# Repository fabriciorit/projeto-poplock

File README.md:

# Trava eletrônica controlada por padrão sonoro
Responsáveis: Caio Vinícius Batista Pereira e Fabrício Ribeiro Toloczko

## Introdução e Justificativa
A automatização residencial tem se tornado cada vez mais comum e mais barata. E uma das facilidades trazidas por este tipo de aplicação tecnológica é a dependência cada vez menor de falhas humanas. É comum as pessoas perderem ou esquecerem as chaves para entrar em casa, e muitas vezes as pessoas tem dificuldades para lembrar senhas. Músicas são trechos sonoros facilmente memorizáveis, além disso extremamente seguros, pois o número de músicas existentes é muito grande e disperso. 

## Especificação do Produto
* Reconhecimento de pelo menos 5 segundos de padrão sonoro;
* Resposta em frequência garantida para frequências médias(200Hz a 1500Hz);
* Tensão de alimentação 110/220V;
* Bateria de emergência;
* Gravação por microfone(eletreto);
* Acionamento de uma trava elétrica 12V de até 1A;
* Comunicação via módulo Wi-Fi usando TCP/IP;
* Interface com usuário via LED;
* Processamento de áudio em servidor alocado em um computador comum.

## Proposta técnica
A pessoa que deseja liberar a trava eletrônica emite um padrão sonoro. Este som é convertido por um sensor(microfone) que alimenta a entrada do microcontrolador. Este, converte o sinal analógico em sinal digital e envia-o pelo módulo de comunicação(Wi-Fi) para um computador, responsável por processar os dados de áudio recebidos.
O computador processará este áudio comparando-o  a um padrão de som de referência previamente configurado, que corresponde à senha de liberação da trava eletrônica. O computador retornará para o microcontrolador um comando de liberação, caso os sinais de áudio sejam considerados iguais, ou de falha de senha, caso os sinais sejam diferentes.
O microcontrolador, por sua vez, aguarda o recebimento de comandos do computador após enviar o som do microfone digitalizado. Ele executará cada comando dependendo de sua função. Duas funções básicas serão destravamento de porta e indicação de falha de senha — via interface com usuário por LED.
Haverá uma fonte de alimentação para os blocos do sistema projetado.

## Proposta de apresentação
Demonstrar o funcionamento do sistema. Este sistema será composto do dispositivo acondicionado em uma caixa plástica e a fechadura representada por uma trava elétrica automotiva — equivalente às de portas residenciais quanto ao princípio de funcionamento. O dispositivo estará ligado a um computador via interface Wi-Fi pela rede convencional.

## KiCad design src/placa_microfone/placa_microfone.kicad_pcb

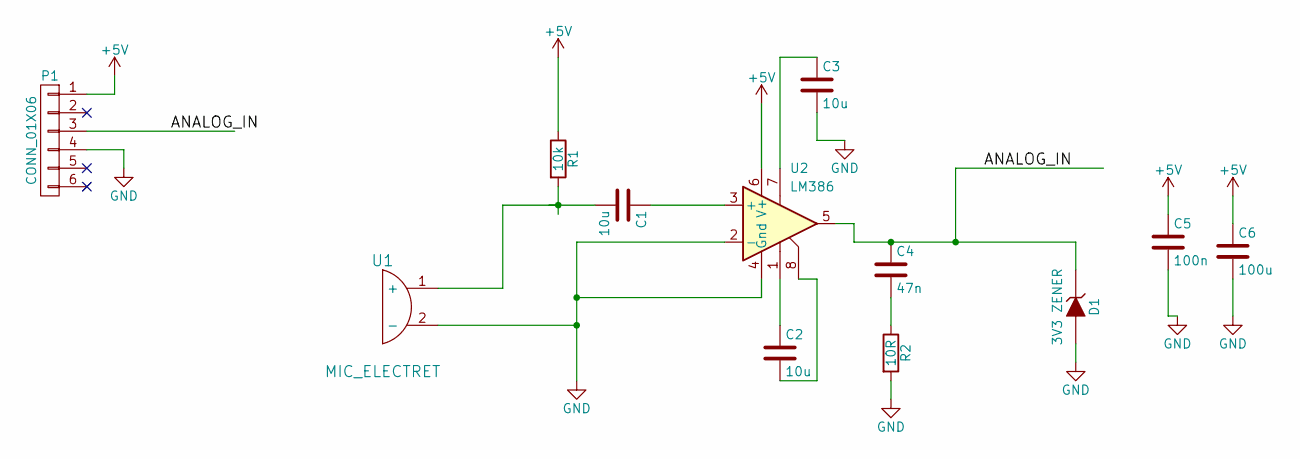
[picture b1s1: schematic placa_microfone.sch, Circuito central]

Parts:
C1, C2, C3: 10u; C_Radial_D5_L6_P2.5
C4: 47n; C_Disc_D3_P2.5
C5: 100n; C_Disc_D3_P2.5
C6: 100u; C_Radial_D5_L6_P2.5
D1: 3V3 ZENER; Diode_DO-35_SOD27_Horizontal_RM10
P1: CONN_01X06; Wafer_Vertical17.5x5.8x7RM2.5-6
R1: 10k; Resistor_Horizontal_RM7mm
R2: 10R; Resistor_Horizontal_RM7mm
U1: MIC_ELECTRET; MagneticBuzzer_Kingstate_KCG0601
U2: LM386; DIP-8_W7.62mm_LongPads

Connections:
+5V: C5.1, C6.1, P1.1, R1.1, U2.6 (V+)
/ANALOG_IN: C4.1, D1.1 (K), P1.3, U2.5
GND: C3.2, C5.2, C6.2, D1.2 (A), P1.4, R2.2, U1.2 (-), U2.2 (-), U2.4 (Gnd)
unnamed: C1.1, U2.3 (+)
unnamed: C1.2, R1.2, U1.1 (+)
unnamed: C2.1, U2.1
unnamed: C2.2, U2.8
unnamed: C3.1, U2.7
unnamed: C4.2, R2.1

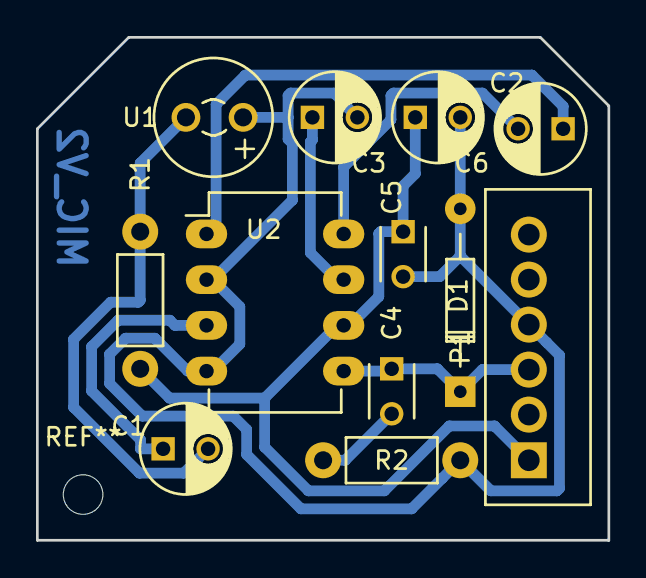
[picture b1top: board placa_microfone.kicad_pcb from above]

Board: 2 copper layers, 31.8 x 27.9 mm, 12 parts (0 on the bottom side), 9 nets.

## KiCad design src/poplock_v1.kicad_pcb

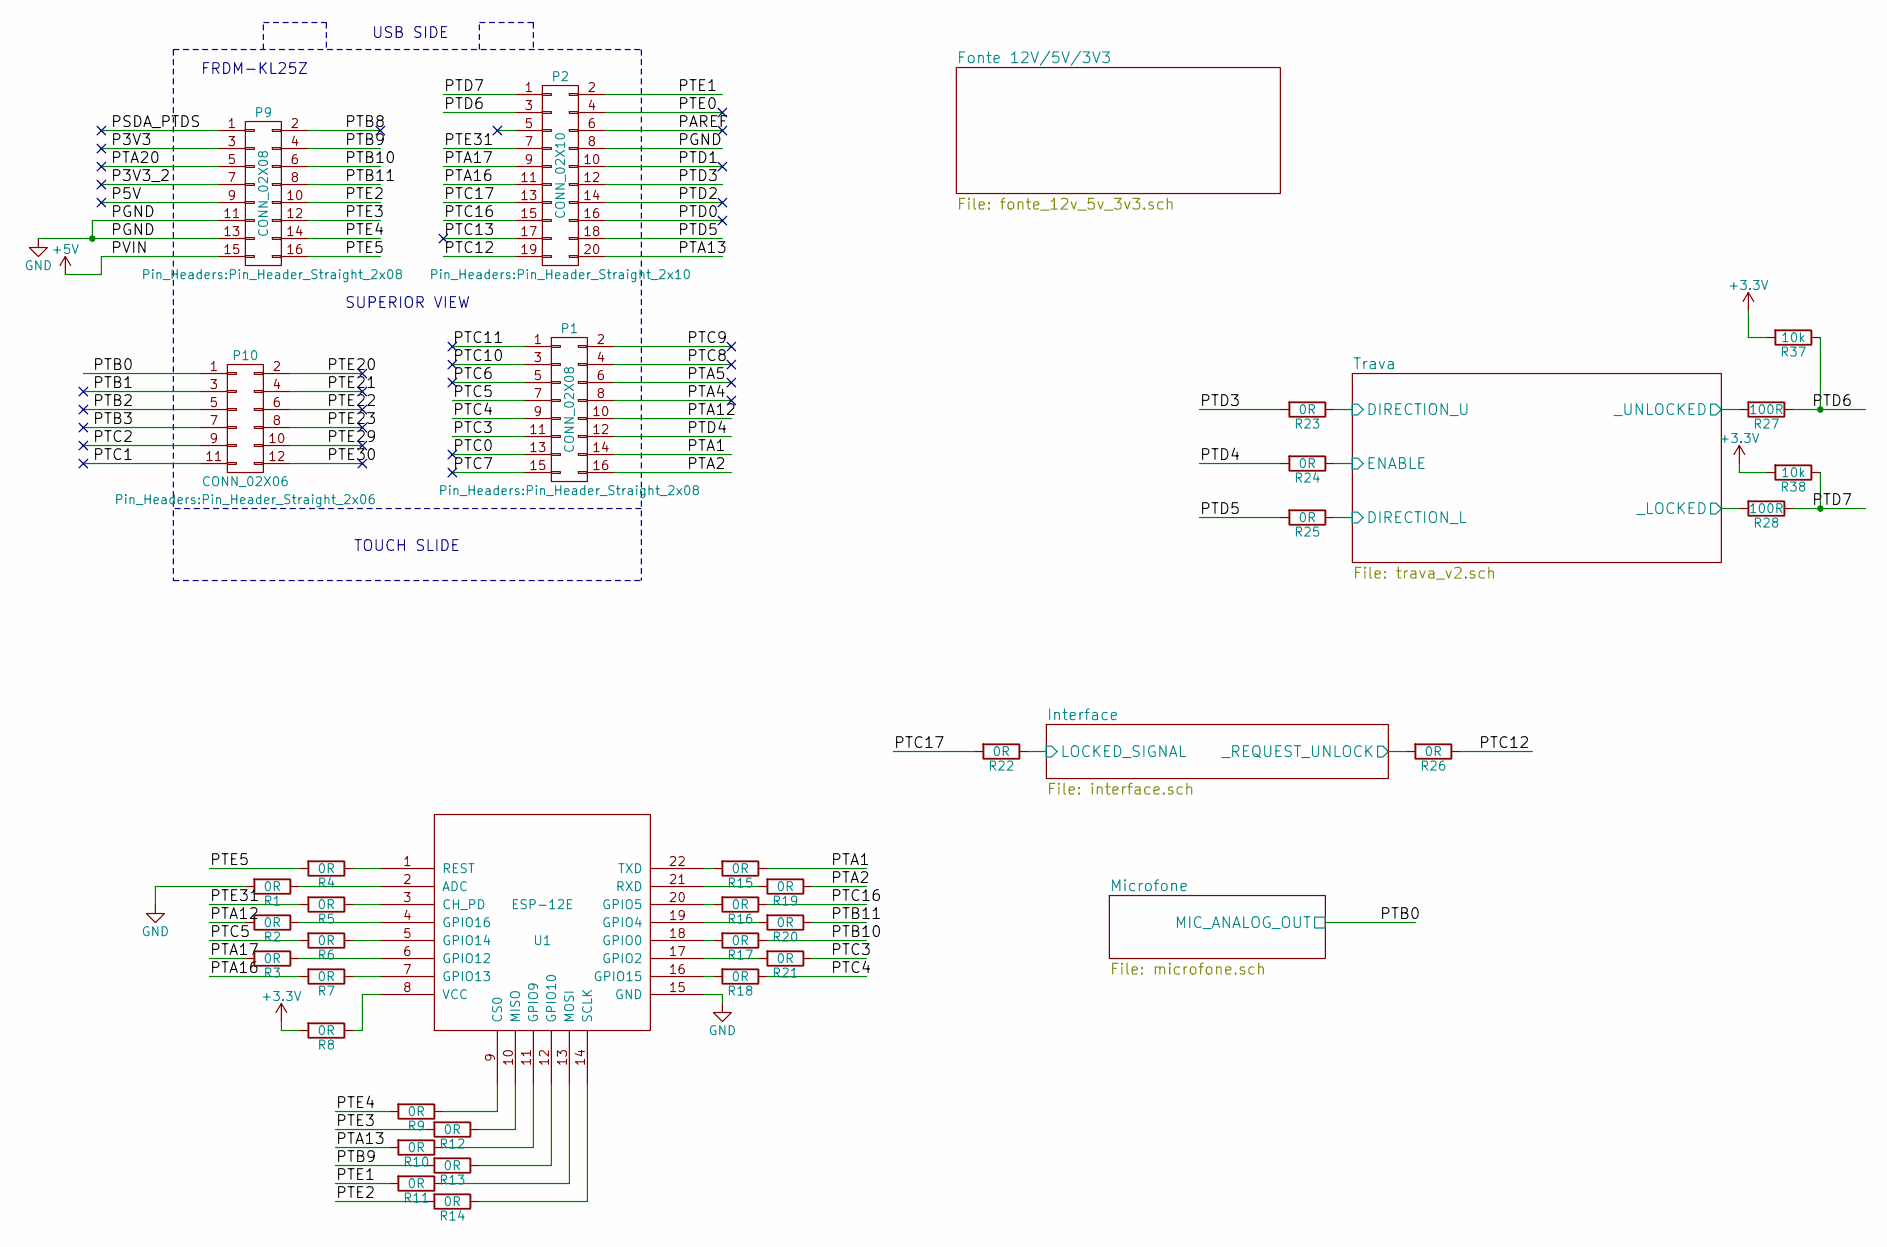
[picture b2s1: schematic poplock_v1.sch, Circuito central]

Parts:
P1, P9: CONN_02X08; Pin_Header_Straight_2x08
P2: CONN_02X10; Pin_Header_Straight_2x10
P10: CONN_02X06; Pin_Header_Straight_2x06
R1, R2, R3, R4, R5, R6, R7, R8, R9, R10, R11, R12, R13, R14, R15, R16, R17, R18, R19, R20, R21, R22, R23, R24, R25, R26: 0R; R_0603_HandSoldering
R27, R28: 100R; R_0603_HandSoldering
R37, R38: 10k; R_0603_HandSoldering
U1: ESP-12E

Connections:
+3V3: R8.2, R37.2, R38.2; also elsewhere on the board
+5V: P9.15; also elsewhere on the board
/Interface/LOCKED_SIGNAL: R22.1; also elsewhere on the board
/Interface/_REQUEST_UNLOCK: R26.2; also elsewhere on the board
/P3V3: P9.3
/P3V3_2: P9.7
/P5V: P9.9
/PAREF: P2.6
/PSDA_PTDS: P9.1
/PTA1: P1.14, R15.1
/PTA2: P1.16, R19.1
/PTA4: P1.8
/PTA5: P1.6
/PTA12: P1.10, R2.2
/PTA13: P2.20, R10.2
/PTA16: P2.11, R7.2
/PTA17: P2.9, R3.2
/PTA20: P9.5
/PTB0: P10.1; also elsewhere on the board
/PTB1: P10.3
/PTB2: P10.5
/PTB3: P10.7
/PTB8: P9.2
/PTB9: P9.4, R13.2
/PTB10: P9.6, R17.1
/PTB11: P9.8, R20.1
/PTC0: P1.13
/PTC1: P10.11
/PTC2: P10.9
/PTC3: P1.11, R21.1
/PTC4: P1.9, R18.1
/PTC5: P1.7, R6.2
/PTC6: P1.5
/PTC7: P1.15
/PTC8: P1.4
/PTC9: P1.2
/PTC10: P1.3
/PTC11: P1.1
/PTC12: P2.19, R26.1
/PTC13: P2.17
/PTC16: P2.15, R16.1
/PTC17: P2.13, R22.2
/PTD0: P2.16
/PTD1: P2.10
/PTD2: P2.14
/PTD3: P2.12, R23.2
/PTD4: P1.12, R24.2
/PTD5: P2.18, R25.2
/PTD6: P2.3, R27.1, R37.1
/PTD7: P2.1, R28.1, R38.1
/PTE0: P2.4
/PTE1: P2.2, R11.2
/PTE2: P9.10, R14.2
/PTE3: P9.12, R12.2
/PTE4: P9.14, R9.2
/PTE5: P9.16, R4.2
/PTE20: P10.2
/PTE21: P10.4
/PTE22: P10.6
/PTE23: P10.8
/PTE29: P10.10
/PTE30: P10.12
/PTE31: P2.7, R5.2
/Trava/DIRECTION_L: R25.1; also elsewhere on the board
/Trava/DIRECTION_U: R23.1; also elsewhere on the board
/Trava/ENABLE: R24.1; also elsewhere on the board
/Trava/_LOCKED: R28.2; also elsewhere on the board
/Trava/_UNLOCKED: R27.2; also elsewhere on the board
GND: P2.8, P9.11, P9.13, R1.2, U1.15 (GND); also elsewhere on the board
unnamed: R1.1, U1.2 (ADC)
unnamed: R2.1, U1.4 (GPIO16)
unnamed: R3.1, U1.6 (GPIO12)
unnamed: R4.1, U1.1 (REST)
unnamed: R5.1, U1.3 (CH_PD)
unnamed: R6.1, U1.5 (GPIO14)
unnamed: R7.1, U1.7 (GPIO13)
unnamed: R8.1, U1.8 (VCC)
unnamed: R9.1, U1.9 (CS0)
unnamed: R10.1, U1.11 (GPIO9)
unnamed: R11.1, U1.13 (MOSI)
unnamed: R12.1, U1.10 (MISO)
unnamed: R13.1, U1.12 (GPIO10)
unnamed: R14.1, U1.14 (SCLK)
unnamed: R15.2, U1.22 (TXD)
unnamed: R16.2, U1.20 (GPIO5)
unnamed: R17.2, U1.18 (GPIO0)
unnamed: R18.2, U1.16 (GPIO15)
unnamed: R19.2, U1.21 (RXD)
unnamed: R20.2, U1.19 (GPIO4)
unnamed: R21.2, U1.17 (GPIO2)

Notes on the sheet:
TOUCH SLIDE
SUPERIOR VIEW
USB SIDE
FRDM-KL25Z

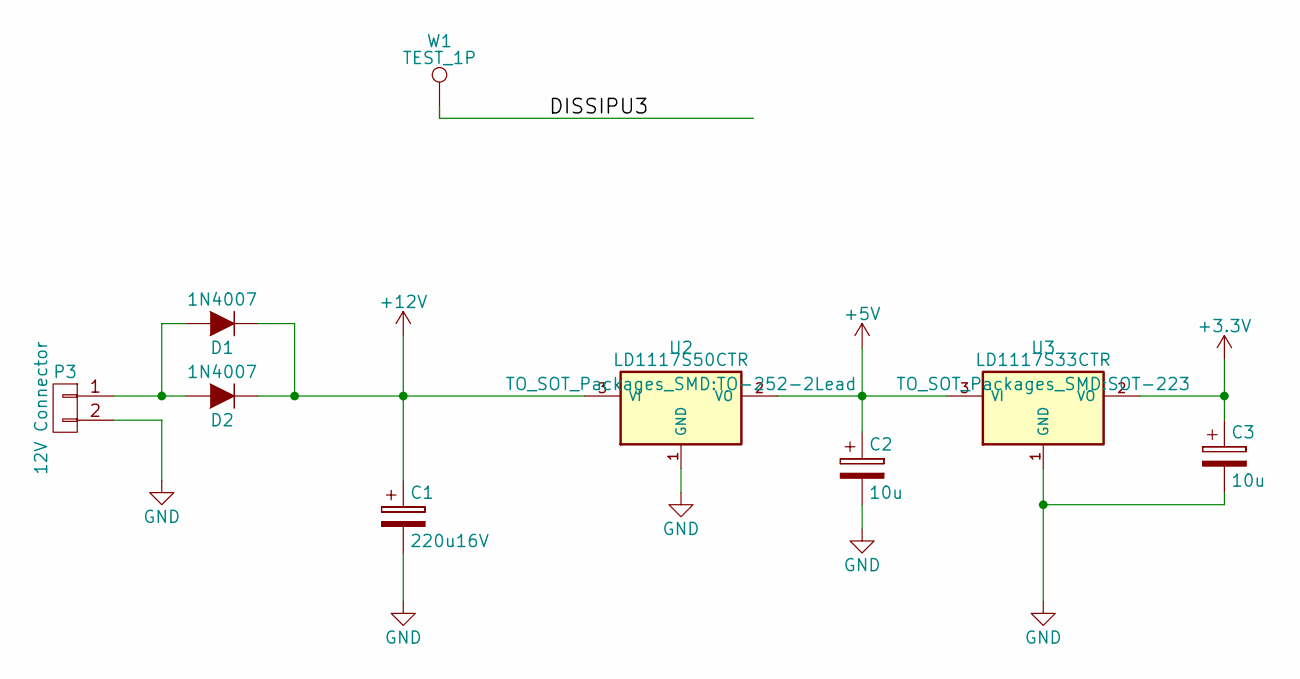
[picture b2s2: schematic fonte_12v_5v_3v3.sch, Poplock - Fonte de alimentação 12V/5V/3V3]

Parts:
C1: 220u16V; Cap_Eletrolitico_8x5
C2, C3: 10u; Cap_Eletrolitico_8x3.5
D1, D2: 1N4007; Diode_DO-41_SOD81_Horizontal_RM10
P3: 12V Connector; BARREL_JACK
U2: LD1117S50CTR; TO-252-2Lead
U3: LD1117S33CTR; SOT-223
W1: TEST_1P; 1Pin

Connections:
+3V3: C3.1, U3.2 (VO); also elsewhere on the board
+5V: C2.1, U2.2 (VO), U3.3 (VI); also elsewhere on the board
+12V: C1.1, D1.1 (K), D2.1 (K), U2.3 (VI); also elsewhere on the board
/Fonte 12V/5V/3V3/DISSIPU3: W1.1
GND: C1.2, C2.2, C3.2, P3.2, U2.1 (GND), U3.1 (GND); also elsewhere on the board
unnamed: D1.2 (A), D2.2 (A), P3.1

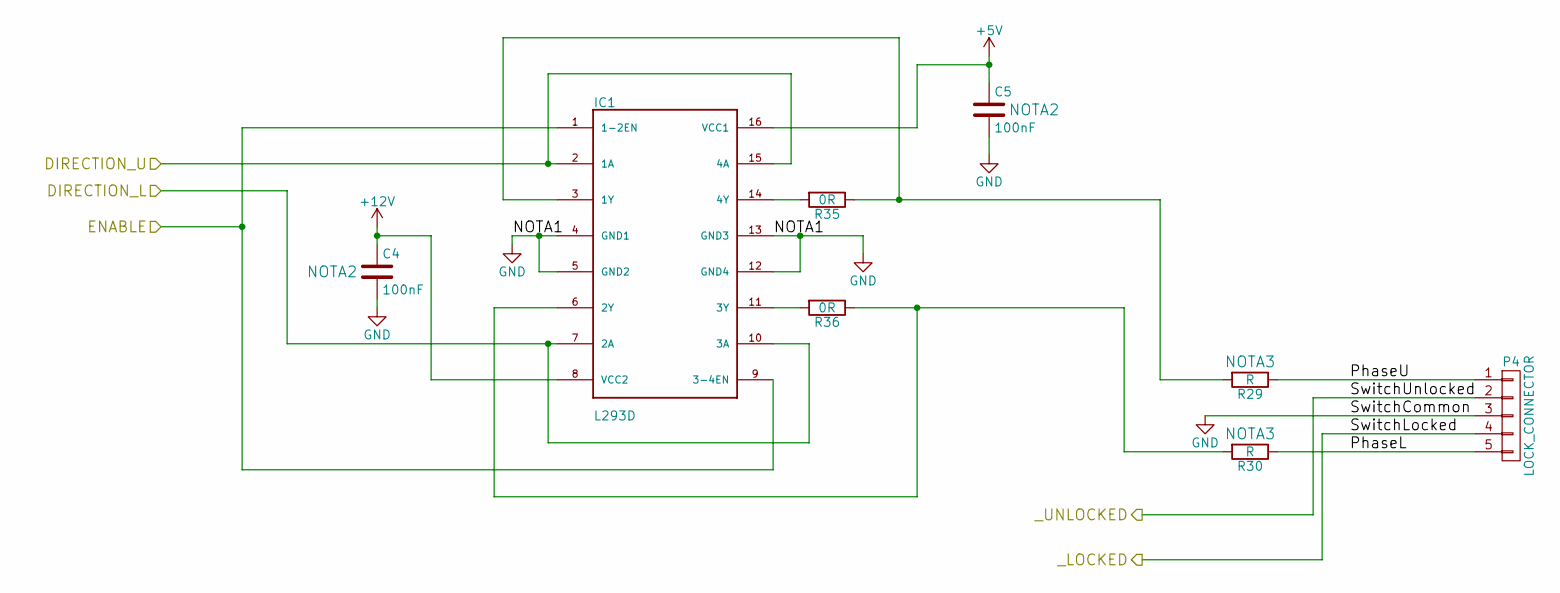
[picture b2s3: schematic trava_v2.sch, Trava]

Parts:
C4, C5: 100nF; Cap_MKT_EPCOS_7,3x2,5
IC1: L293D; DIP-16_W7.62mm_LongPads
P4: LOCK_CONNECTOR; Wafer_Vertical15x5.8x7RM2.5-5
R29, R30: R; Resistor_Horizontal_RM15mm
R35, R36: 0R; R_1210_HandSoldering

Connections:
+5V: C5.1, IC1.16 (VCC1); also elsewhere on the board
+12V: C4.1, IC1.8 (VCC2); also elsewhere on the board
/Trava/DIRECTION_L: IC1.7 (2A), IC1.10 (3A); also elsewhere on the board
/Trava/DIRECTION_U: IC1.2 (1A), IC1.15 (4A); also elsewhere on the board
/Trava/ENABLE: IC1.1 (1-2EN), IC1.9 (3-4EN); also elsewhere on the board
/Trava/PhaseL: P4.5, R30.1
/Trava/PhaseU: P4.1, R29.1
/Trava/_LOCKED: P4.4; also elsewhere on the board
/Trava/_UNLOCKED: P4.2; also elsewhere on the board
GND: C4.2, C5.2, IC1.4 (GND1), IC1.5 (GND2), IC1.12 (GND4), IC1.13 (GND3), P4.3; also elsewhere on the board
unnamed: IC1.3 (1Y), R29.2, R35.1
unnamed: IC1.6 (2Y), R30.2, R36.1
unnamed: IC1.11 (3Y), R36.2
unnamed: IC1.14 (4Y), R35.2

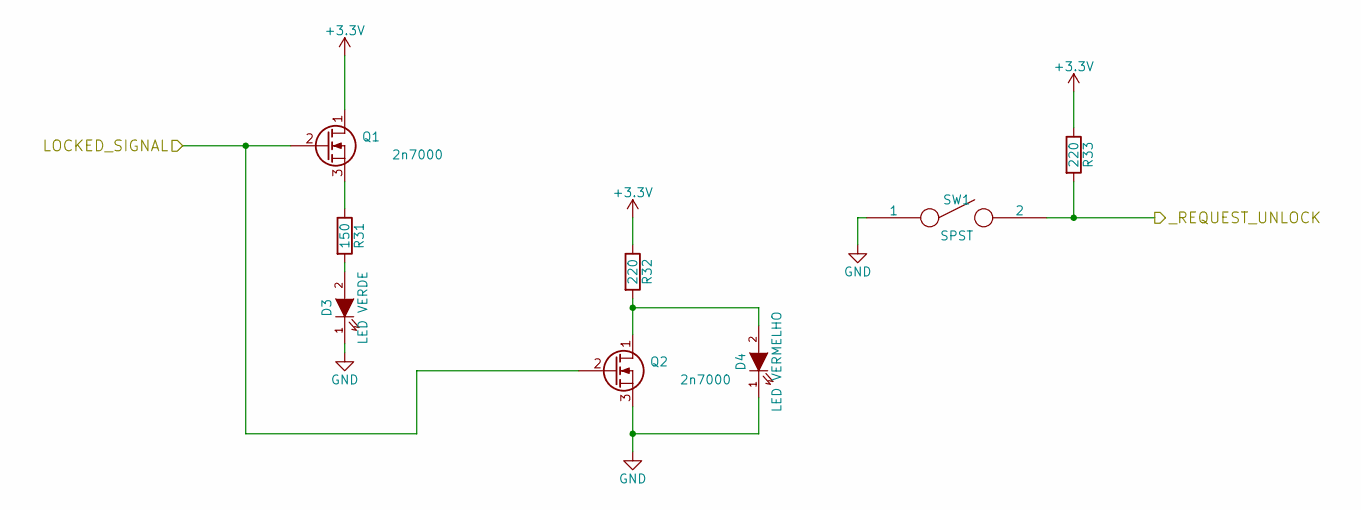
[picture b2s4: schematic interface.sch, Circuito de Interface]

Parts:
D3: LED VERDE; LED-5MM
D4: LED VERMELHO; LED-5MM
Q1, Q2: 2n7000; TO-92_Inline_Narrow_Oval
R31: 150; Resistor_Horizontal_RM7mm
R32, R33: 220; Resistor_Horizontal_RM7mm
SW1: SPST; SW_PUSH-12mm

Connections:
+3V3: Q1.1 (D), R32.1, R33.1; also elsewhere on the board
/Interface/LOCKED_SIGNAL: Q1.2 (G), Q2.2 (G); also elsewhere on the board
/Interface/_REQUEST_UNLOCK: R33.2, SW1.2; also elsewhere on the board
GND: D3.1 (K), D4.1 (K), Q2.3 (S), SW1.1; also elsewhere on the board
unnamed: D3.2 (A), R31.2
unnamed: D4.2 (A), Q2.1 (D), R32.2
unnamed: Q1.3 (S), R31.1

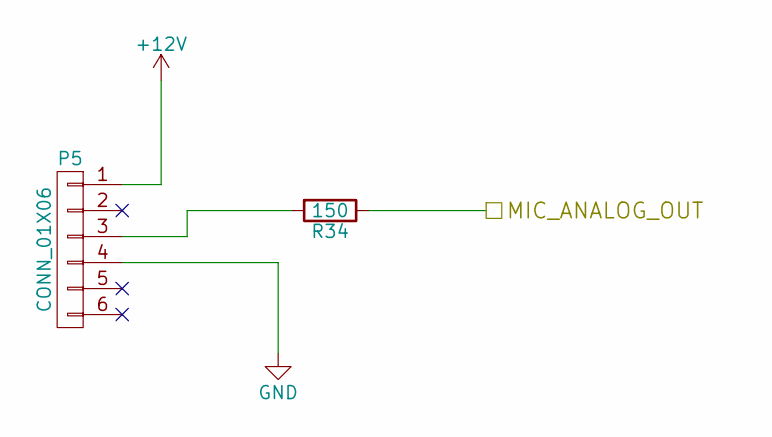
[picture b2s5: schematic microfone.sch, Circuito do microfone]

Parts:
P5: CONN_01X06; Wafer_Vertical17.5x5.8x7RM2.5-6
R34: 150; Resistor_Horizontal_RM7mm

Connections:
+12V: P5.1; also elsewhere on the board
/PTB0: R34.1; also elsewhere on the board
GND: P5.4; also elsewhere on the board
unnamed: P5.3, R34.2

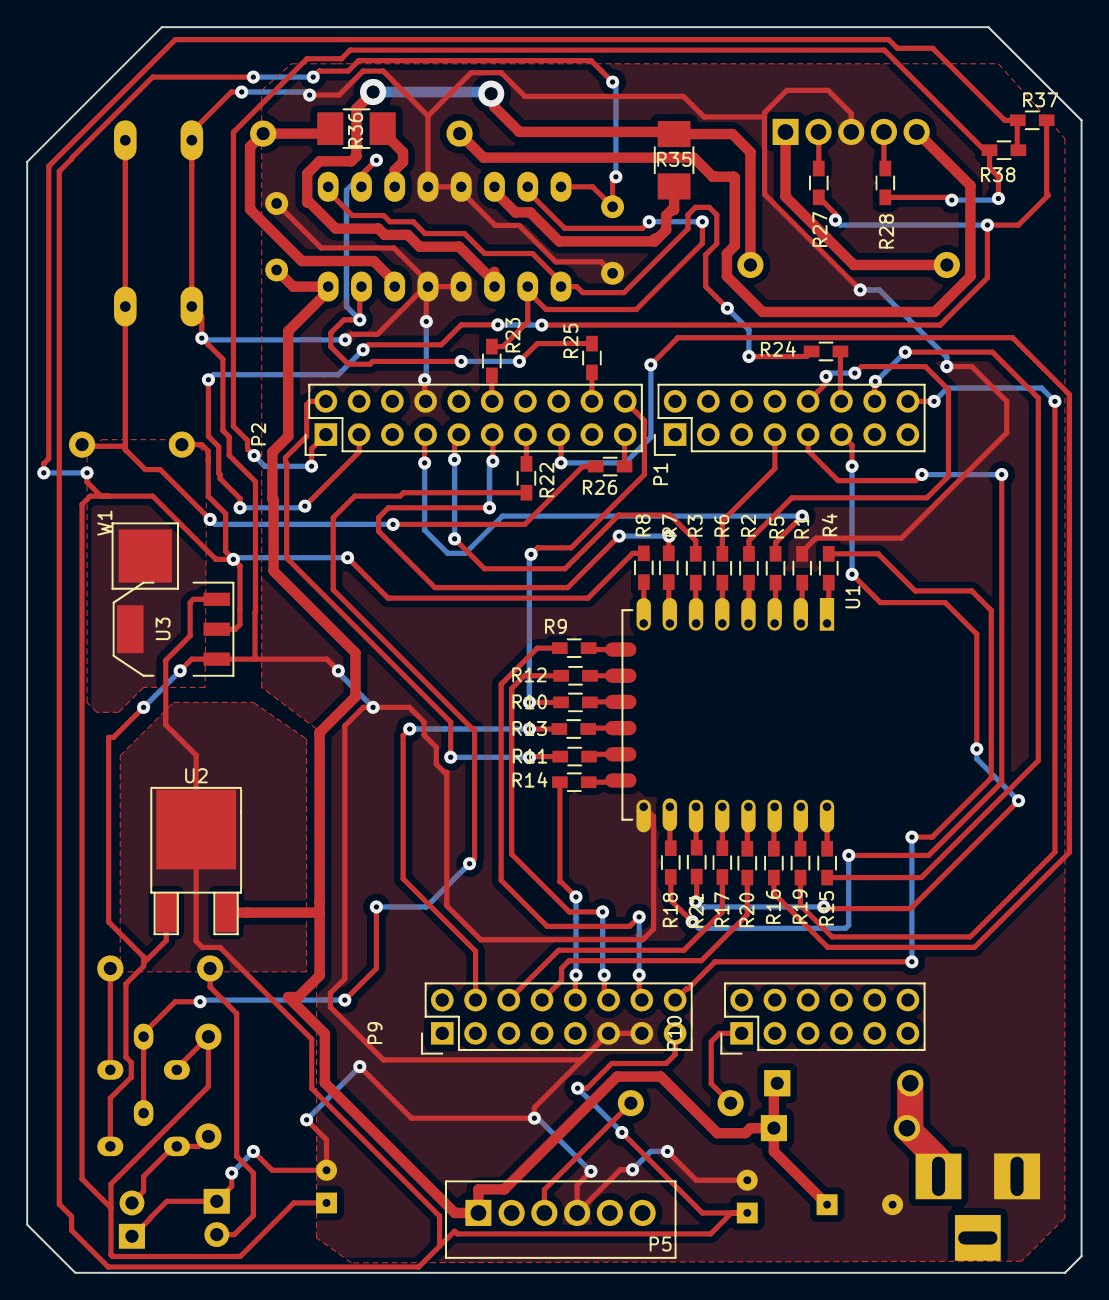
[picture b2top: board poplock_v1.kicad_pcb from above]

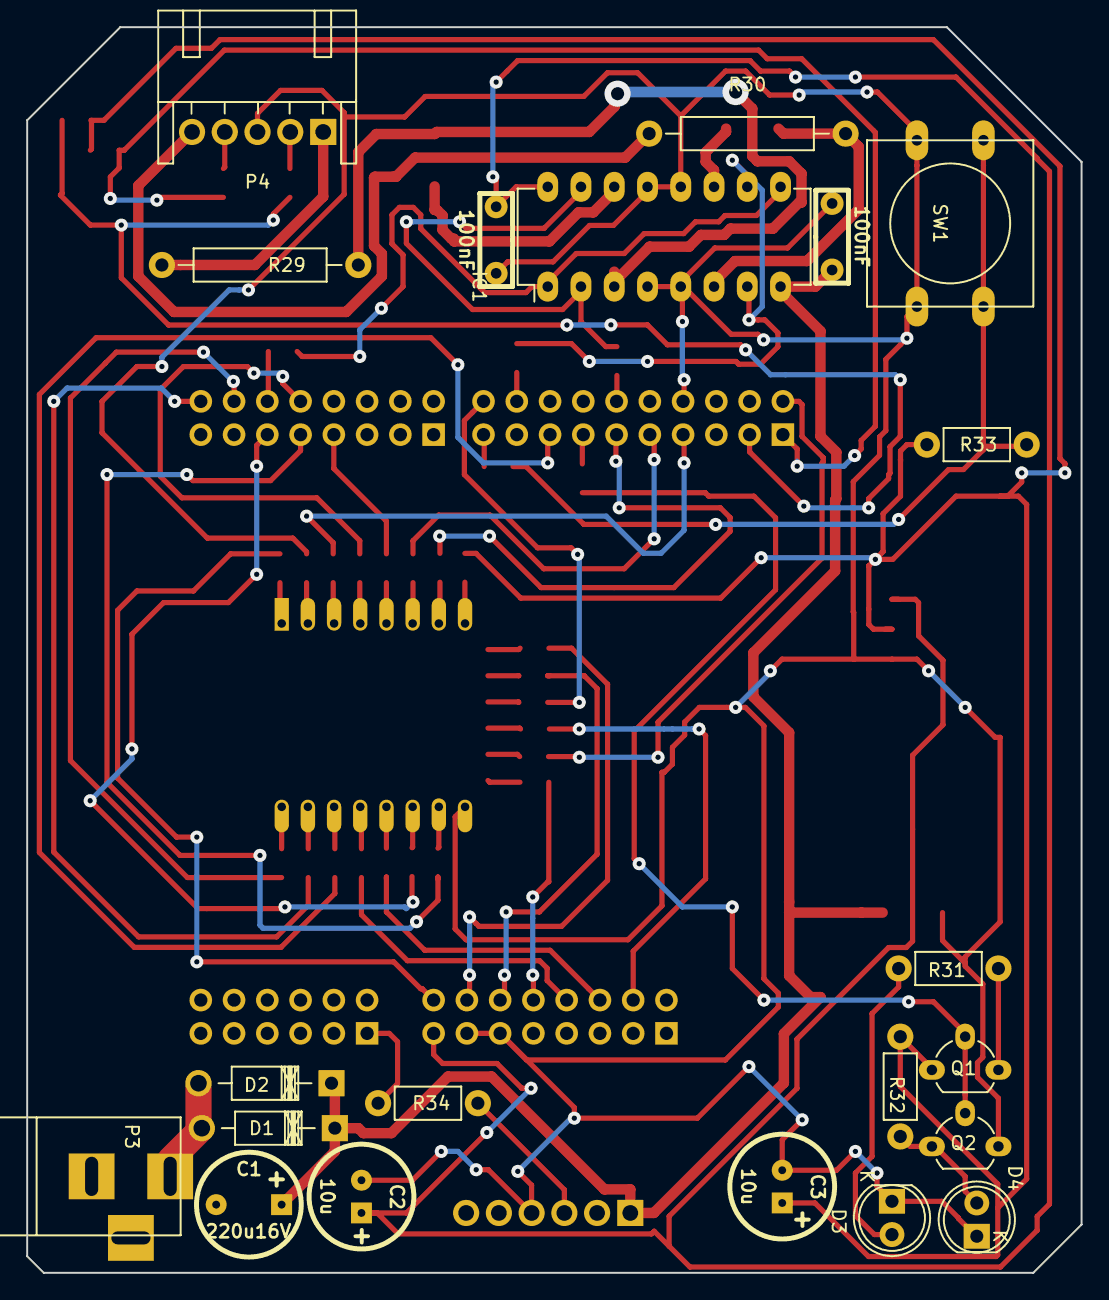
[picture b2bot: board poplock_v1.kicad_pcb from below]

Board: 2 copper layers, 80.5 x 95.1 mm, 62 parts (21 on the bottom side), 70 nets.

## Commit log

2016-08-26 add README
2016-08-28 primeira versao do circuito da trava eletrica e da fonte de alimentacao
2016-09-05 Modifiquei alguns arquivos e criei uma hierarquia no circuito.
2016-09-05 cicuito mic sem hierarquia
2016-09-05 Módulo de interface
2016-09-05 Criada hierarquia para o circuito do microfone
2016-09-07 Adicionados conectores da FRDM-KL25Z e conexões básicas de alimentação
2016-09-07 Tabela de pinos ESP12E e FRDM-KL25Z
2016-09-07 Atualização da tabela de pinos acrescentando os outros módulos(microfone e trava)
2016-09-08 Acréscimo de bibliotecas de símbolo e de footprint do ESP12E retiradas de https://github.com/jdunmire/kicad-ESP8266 . As conexões necessárias com a KL25Z também foram realizadas.
2016-09-08 Substituição dos transitores NMOS pelo transistor 2n7000
2016-09-08 Verificação ERC -- checagem de erros elétricos no esquema -- concluída com sucesso. Há apenas dois warnings que não indicam problemas.
2016-09-09 Footprint atualizado
2016-09-09 Movida a pasta lib para dentro da pasta src. Preparado o arquivo de netlist e o da edição da PCB. A mudança de pastas permite referenciar os componentes usando variáveis de ambiente no KiCAD. Isso el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
2016-09-10 Definidas as dimensões necessárias(posição dos conectores, furos e bordas da FRDM-KL25Z) para criação do shield
2016-09-10 Corrigidas dimensões de comprimento da placa que estavam referenciadas num ponto errado.
2016-09-10 Distribuidos os componentes sobre a placa.
2016-09-20 Gerada a lista de materiais(BOM)
2016-09-22 Removi circuito de microfone e coloquei conector de 6 pinos, além de um resistor para proteção. O conector pode ser invertido sem problemas de danos à placa. Há um novo projeto dentro da pasta placa_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
2016-09-23 PCB completa, feita a primeira revisão.
2016-09-24 Modificacao footprint regulador 5v
2016-09-24 Preparo do Silk da poplock v1
2016-09-24 Preparo do Silk da poplock v1 - correcao de textos
2016-09-26 Desenvolvida PCB para circuito mic_v2
2016-09-26 PDF da mic_v2
2016-11-18 Pequenas modificacoes nos pinos utilizados pelo projeto -- apenas planilha de pinos, pĺaca e outros arquivos nao foram alterados
2022-04-11 Update LICENSE
